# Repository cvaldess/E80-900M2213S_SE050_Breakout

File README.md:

# E80-900M2213S + SE050 Breakout

A breakout board for the **Ebyte E80-900M2213S** dual-band LoRa module (Semtech **LR1121**, sub-GHz
and 2.4 GHz) with an **NXP EdgeLock SE050E2** secure element next to it. The radio's SPI bus and
control lines and the secure element's I²C bus all come out on one 14-pin 2.54 mm header. Each antenna
port has its own right-angle SMA connector, fed by a 50 Ω line.

68.92 × 51.80 mm, two layers, 1.6 mm, four M2.5 mounting holes. Designed in KiCad 10. The project is
self-contained: the symbols, footprints and 3D models of every non-standard part are in [`lib/`](lib/),
so it opens on any machine without installing extra libraries.

> **Status: not fabricated yet.** The design passes DRC, ERC and schematic parity with zero
> violations, but no board has been built or tested. The RF line impedance is calculated, not
> measured. Read [Fabrication](#fabrication) before ordering.

## Made with Claude and Konnect

This board was designed by [cvaldess](https://github.com/cvaldess) with the help of **Claude**
(Anthropic's AI model), working on the KiCad project through
**[Konnect](https://github.com/mixelpixx/Konnect)**, an MCP server that lets an AI agent read,
check and edit KiCad designs through KiCad's own tooling instead of rewriting the files as text.

Claude reviewed the RF layout against the module's manual, reshaped the two antenna feed lines,
checked the design rules, added the 3D models and generated the fabrication files. It did this through
Konnect, together with KiCad's own command-line and Python tools. Commits it co-authored carry its
`Co-Authored-By` line.

## Pinout (J2, 1×14, 2.54 mm pitch)

| Pin | Signal | Connects to | Notes |
|----|--------|-------------|-------|
| 1 | 3V3 | E80 VCC (pin 25), SE050 VIN | the only supply; powers the whole board |
| 2 | MISO | E80 pin 3 | LR1121 SPI |
| 3 | MOSI | E80 pin 4 | LR1121 SPI |
| 4 | SCK | E80 pin 5 | LR1121 SPI |
| 5 | NSS | E80 pin 6 | SPI chip select |
| 6 | BUSY | E80 pin 7 | |
| 7 | DIO7 | E80 pin 24 | LR1121 I/O, see below |
| 8 | DIO8 | E80 pin 23 | LR1121 I/O, see below |
| 9 | DIO9 | E80 pin 22 | LR1121 radio interrupt, see below |
| 10 | NRST | E80 pin 21 | 10 kΩ pull-up and 100 nF to GND on board |
| 11 | ENA | SE050 ENA | **must be driven high**, see below |
| 12 | SDA | SE050 I²C data | 4.7 kΩ pull-up on board |
| 13 | SCL | SE050 I²C clock | 4.7 kΩ pull-up on board |
| 14 | GND | | |

**Pin 9 is the radio's interrupt line, DIO9.** Host code written for SX126x radios often calls
this pin DIO1, but on the LR1121 the interrupt comes out on DIO9 (module pin 22), and the board uses
the module's name. Point your driver's IRQ pin at it.

**DIO7 and DIO8** (module pins 24 and 23) come out on pins 7 and 8. Ebyte's manual lists them as
LR1121 input/output lines and refers to the chip's datasheet for their use. Leave them unconnected if
you don't need them.

**ENA is not optional.** R3 (100 kΩ) pulls it to ground, so the SE050 powers up in deep power-down
and will **not answer on I²C** until the host drives ENA high. If a bus scan finds nothing at
**0x48**, this is the reason. Unlike the standalone
[SE050 breakout](https://github.com/cvaldess/se050-breakout), this board has no solder jumper to
tie ENA high. If you have no GPIO to spare, connect pin 11 to 3V3 externally.

All logic is 3.3 V.

## Board

## Bill of materials

| Ref | Value | Footprint | Purpose |
|-----|-------|-----------|---------|
| U1 | Ebyte E80-900M2213S | 26-position castellated module | LR1121 dual-band LoRa radio |
| IC2 | NXP SE050E2HQ1/Z01Z3Z | HX2QFN20, 3 × 3 mm | secure element |
| SMA1, SMA2 | HJ-SMA175 (LCSC C1509213) | right-angle SMA jack, through-hole | 2.4 GHz and sub-GHz antenna ports |
| C9 | 22 µF / 6.3 V (LCSC C2161824) | aluminium polymer, SMD Ø4 × 5.5 mm | bulk capacitance on the module supply, 200 mΩ ESR |
| C5 | 100 nF | 0603 | module decoupling |
| C8 | 100 nF | 0603 | SE050 VIN decoupling |
| C10 | 100 nF | 0603 | NRST filter |
| C6 | 33 nF | 0603 | ENA filter |
| R4, R5 | 4.7 kΩ | 0603 | I²C pull-ups (SCL, SDA) |
| R6 | 10 kΩ | 0603 | NRST pull-up |
| R3 | 100 kΩ | 0603 | ENA pull-down |
| J2 | 1×14 pin header | 2.54 mm pitch | host connector |
| H1–H4 | — | M2.5, plated, tied to GND | mounting holes |

SMA1 is the **2.4 GHz** port (module pin 12) and SMA2 the **sub-GHz** port (module pin 15, labelled
868 MHz on the silkscreen). Both pin assignments were checked against the drawing in Ebyte's
E80-xxxM2213S user manual.

## Design notes

**RF feed lines.** Both antenna ports use grounded coplanar waveguide on the top layer: a 1.35 mm
track with a 0.35 mm gap to the ground pour, with ground poured on both layers and stitched with via
fences along each line. On the stack-up declared in the project (1.6 mm, 1.51 mm core, εr 4.5) that
works out at about 49.5–55 Ω, depending on the calculation model. Each line leaves the module's
antenna pad through a short 0.8 mm neck (the pad is narrower than the line), runs straight, turns
through a single tangent arc of 2 mm radius, and runs straight into the SMA centre pin.

**Clearances come from rules, not from hand edits.** The ground pour is set to the 0.35 mm RF gap.
A custom rule in [`E80-900M2213S_SE050_Breakout.kicad_dru`](E80-900M2213S_SE050_Breakout.kicad_dru)
moves it back to 0.5 mm from everything else. A second rule opens a 1.0 mm anti-pad around the SMA
centre pins on both layers, which reduces the capacitance of the through-hole transition. If you change
the gap, refill the zones before plotting. `kicad-cli pcb drc --refill-zones --save-board` does it
from the command line with the project's own rules.

**The SE050 circuit is the one from [se050-breakout](https://github.com/cvaldess/se050-breakout)**,
where an earlier revision was built and validated on hardware. VOUT and VCC are tied together with no
capacitor, RST_N goes to ground and the ISO7816 pins are left unconnected. The reasons for each of
these are in that repository's design notes. The exposed pad goes to ground through the same five
0.3 mm vias, one in the centre and one under each of the four paste windows. What is different here:
0603 passives, no ENA jumper, and the I²C pull-ups share the header with the radio.

**Module footprint.** The E80 has 26 positions but only 22 pads (positions 9, 10, 17 and 18 do not
exist). The footprint in `lib/` follows Ebyte's drawing. If you start from Ebyte's own Altium library
instead, note that its pin labels belong to a different, UART-based module. They were corrected here
against the user manual and moved to the fabrication layer.

**3D models.** The SMA model is the manufacturer's STEP file, positioned from its own geometry and
checked against the connector's datasheet (6 × 6 mm body, 17 mm long, 9.5 mm high with 3.3 mm pins).
The thread overhangs the bottom edge of the board.

## Fabrication

Everything a board house needs is in [`gerber/`](gerber/), and the same files are zipped in
[`E80-900M2213S_SE050_Breakout_gerber.zip`](E80-900M2213S_SE050_Breakout_gerber.zip) for upload:

- Gerber X2 for both copper layers, both solder masks, the top silkscreen, both paste layers and the
  board outline, plus the Gerber job file
- Excellon drill files, plated and non-plated separately, with drill maps

There is **no bottom silkscreen**. All 297 holes are plated (237 of them are 0.3 mm vias). The
smallest track and clearance are 0.2 mm, which is within any standard two-layer service.

**Before ordering, check the RF gap against your fab's stack-up.** The 4.5 permittivity and 1.51 mm
core in the project are generic FR-4 assumptions. Put 1.35 mm / 0.35 mm through your board house's
impedance calculator with the stack-up it actually uses for 1.6 mm two-layer boards. If the result is
far from 50 Ω, change the ground zone's clearance, refill the zones and regenerate the gerbers.

> **Fabrication status, precisely.** This board has not been manufactured. Nothing on it has been
> measured, including the line impedance and the SMA transition, which are analytic estimates only.
> The SE050 section repeats a circuit that has been validated on another board. The radio section has
> not been validated. Treat a first order as a prototype run. There is no pick-and-place or assembly
> BOM file yet.

## Repository layout

```
E80-900M2213S_SE050_Breakout.kicad_pro / .kicad_sch / .kicad_pcb
E80-900M2213S_SE050_Breakout.kicad_dru      custom clearance rules for the RF section
sym-lib-table / fp-lib-table                 project library tables, pointing into lib/ via ${KIPRJMOD}
lib/                                         symbols, footprints and 3D models (E80, SE050, SMA)
gerber/                                      fabrication output
E80-900M2213S_SE050_Breakout_gerber.zip      the same fabrication output, zipped
E80-900M2213S_SE050_Breakout-3D.JPG          3D render
E80-900M2213S_SE050_Breakout-2D.JPG          bare board
```

## License

GPL-3.0, see [LICENSE](LICENSE). The 3D models of third-party parts in `lib/` come from their
manufacturers and are included so the project opens complete.

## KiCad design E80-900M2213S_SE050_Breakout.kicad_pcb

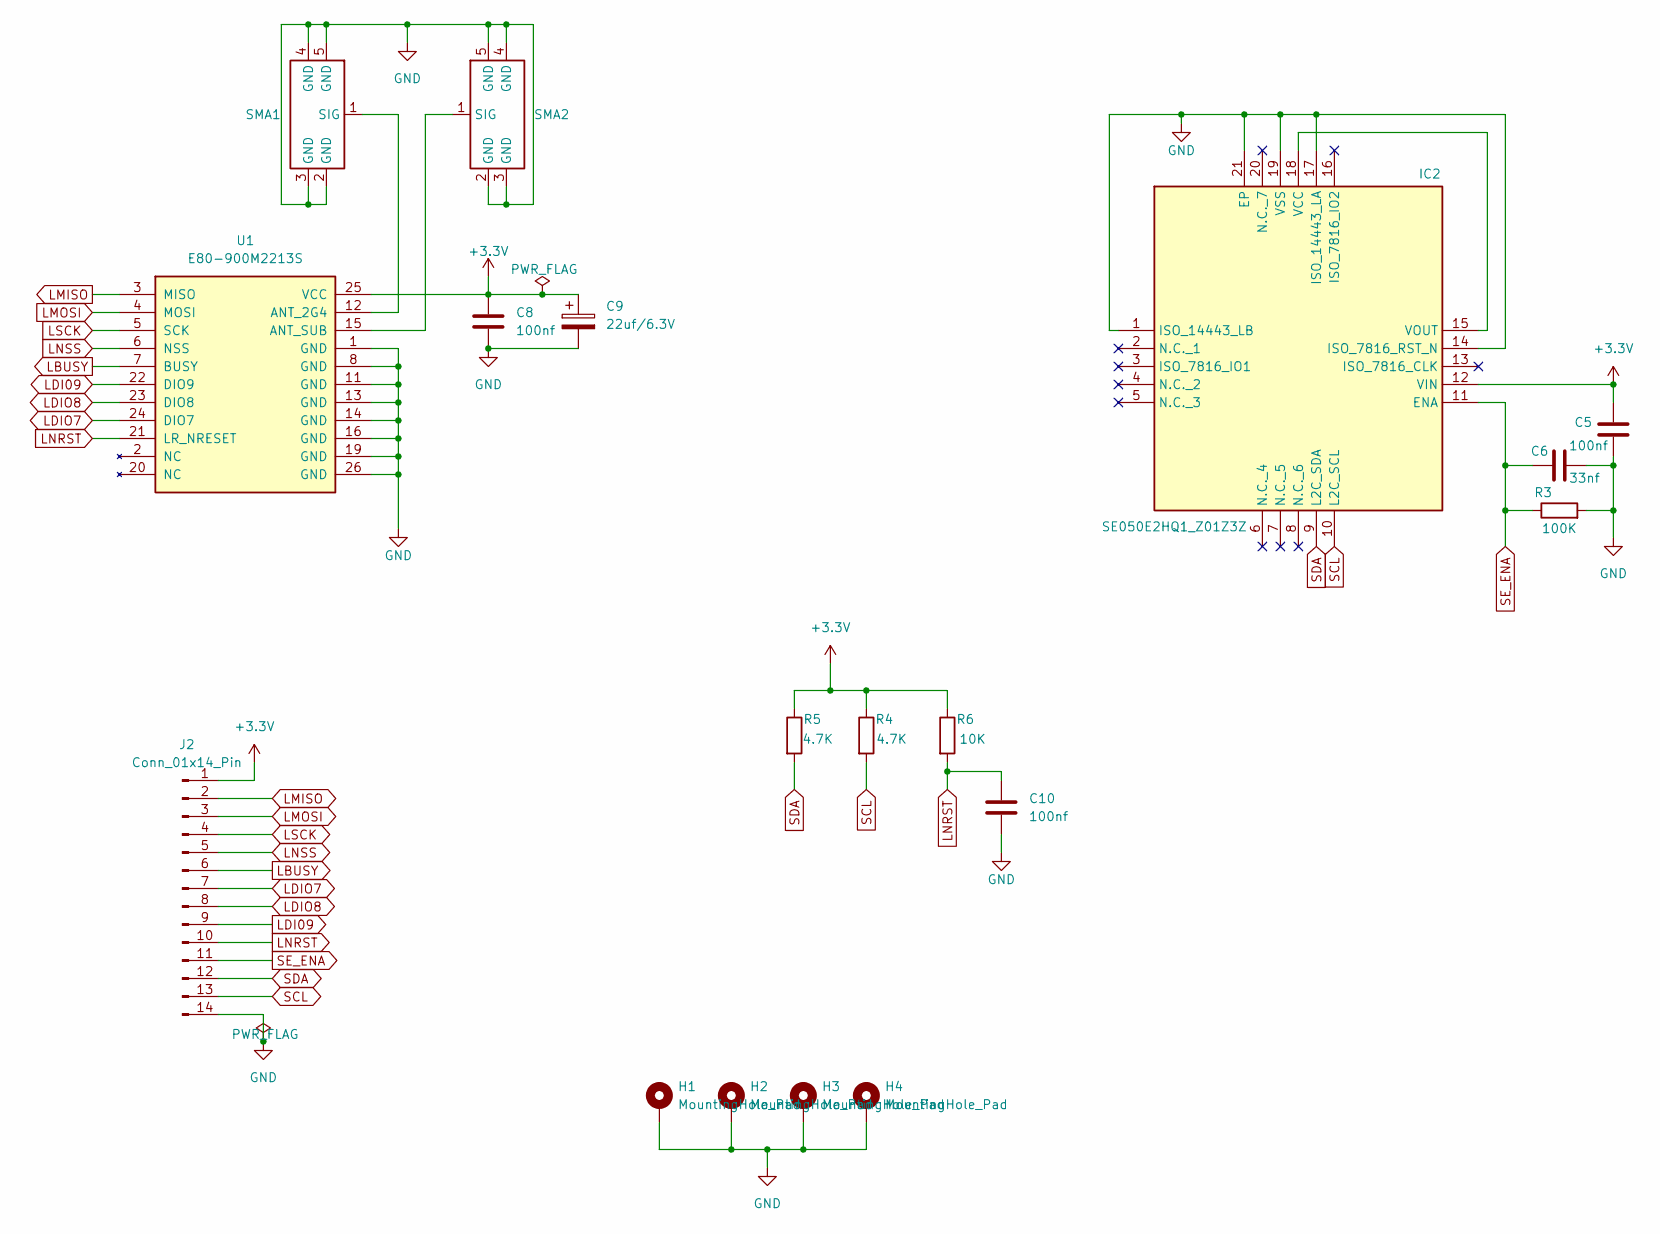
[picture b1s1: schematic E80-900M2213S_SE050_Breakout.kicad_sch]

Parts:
C5, C8, C10: 100nf; C_0603_1608Metric
C6: 33nf; C_0603_1608Metric
C9: 22uf/6.3V; CP_Elec_4x5.4; LCSC Part Name C2161824
H1, H2, H3, H4: MountingHole_Pad; MountingHole_2.7mm_M2.5_Pad_Via
IC2: SE050E2HQ1_Z01Z3Z; QFN40P300X300X33-21N-D; Manufacturer_Part_Number SE050E2HQ1/Z01Z3Z; Mouser Part Number 771-SE050E2HQ1Z01Z3Z
J2: Conn_01x14_Pin; PinHeader_1x14_P2.54mm_Vertical
R3: 100K; R_0603_1608Metric
R4, R5: 4.7K; R_0603_1608Metric
R6: 10K; R_0603_1608Metric
SMA1, SMA2: -; SMA-TH_HJ-SMA175; Manufacturer Part HJ-SMA175; LCSC Part Name 两件套 内孔 SMA 弯头
U1: E80-900M2213S; E80-xxxM2213S; MPN E80-900M2213S

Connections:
+3.3V: C5.1, C8.1, C9.1, IC2.12 (VIN), J2.1, R4.1, R5.1, R6.1, U1.25 (VCC)
GND: C5.2, C6.1, C8.2, C9.2, C10.2, H1.1 (1_1), H2.1 (1_1), H3.1 (1_1), H4.1 (1_1), IC2.1 (ISO_14443_LB), IC2.14 (ISO_7816_RST_N), IC2.17 (ISO_14443_LA), IC2.19 (VSS), IC2.21 (EP), J2.14, R3.2, SMA1.2 (GND), SMA1.3 (GND), SMA1.4 (GND), SMA1.5 (GND), SMA2.2 (GND), SMA2.3 (GND), SMA2.4 (GND), SMA2.5 (GND), U1.1 (GND), U1.8 (GND), U1.11 (GND), U1.13 (GND), U1.14 (GND), U1.16 (GND), U1.19 (GND), U1.26 (GND)
LBUSY: J2.6, U1.7 (BUSY)
LDI09: J2.9, U1.22 (DIO9)
LDIO7: J2.7, U1.24 (DIO7)
LDIO8: J2.8, U1.23 (DIO8)
LMISO: J2.2, U1.3 (MISO)
LMOSI: J2.3, U1.4 (MOSI)
LNRST: C10.1, J2.10, R6.2, U1.21 (LR_NRESET)
LNSS: J2.5, U1.6 (NSS)
LSCK: J2.4, U1.5 (SCK)
unnamed: IC2.15 (VOUT), IC2.18 (VCC)
unnamed: SMA1.1 (SIG), U1.12 (ANT_2G4)
unnamed: SMA2.1 (SIG), U1.15 (ANT_SUB)
SCL: IC2.10 (L2C_SCL), J2.13, R4.2
SDA: IC2.9 (L2C_SDA), J2.12, R5.2
SE_ENA: C6.2, IC2.11 (ENA), J2.11, R3.1

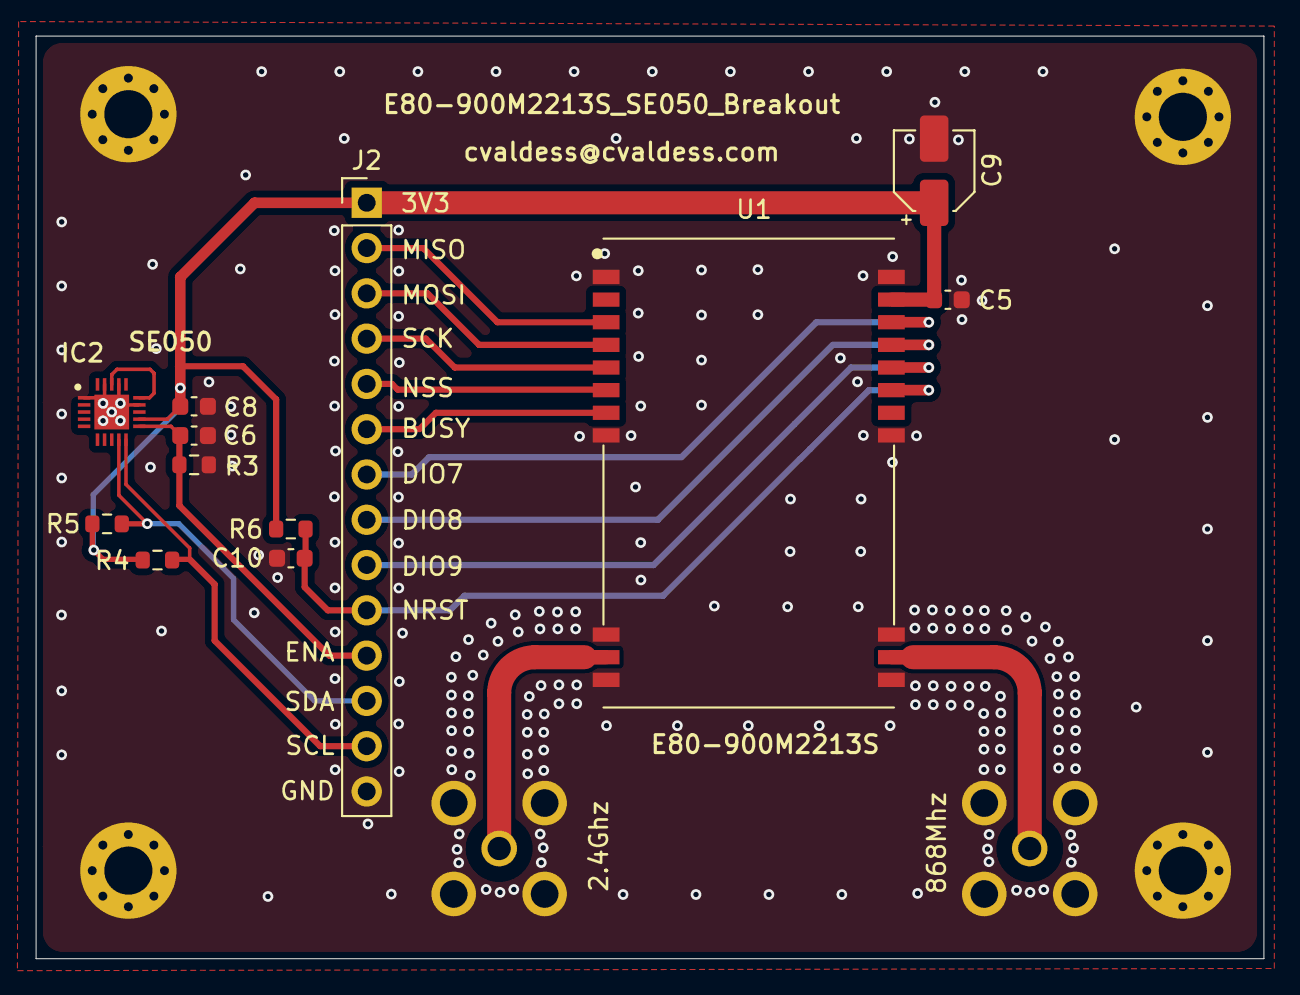
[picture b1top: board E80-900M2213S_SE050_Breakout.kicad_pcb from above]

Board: 2 copper layers, 68.9 x 51.8 mm, 18 parts (0 on the bottom side), 17 nets.
